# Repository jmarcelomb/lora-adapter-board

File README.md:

Adataper board for [LoRa LLCC68 module](https://pt.aliexpress.com/item/1005005763543912.html?gatewayAdapt=glo2bra) with 2 mm pin spacing.

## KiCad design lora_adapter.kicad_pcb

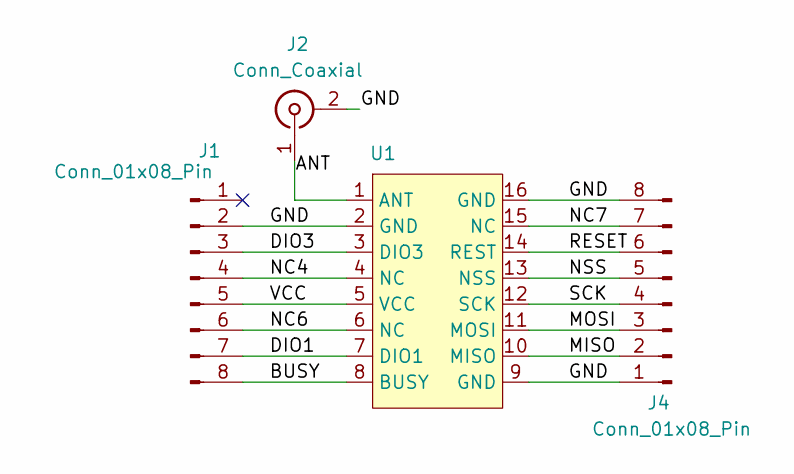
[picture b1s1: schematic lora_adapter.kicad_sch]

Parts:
J1, J4: Conn_01x08_Pin; PinHeader_1x08_P2.54mm_Vertical
J2: Conn_Coaxial; U.FL_Molex_MCRF_73412-0110_Vertical
U1: HOPERF_RFM9XW_SMD

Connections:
/ANT: J2.1 (In), U1.1 (ANT)
/BUSY: J1.8, U1.8 (BUSY)
/DIO1: J1.7, U1.7 (DIO1)
/DIO3: J1.3, U1.3 (DIO3)
/GND: J1.2, J2.2 (Ext), J4.1, J4.8, U1.2 (GND), U1.9 (GND), U1.16 (GND)
/MISO: J4.2, U1.10 (MISO)
/MOSI: J4.3, U1.11 (MOSI)
/NC4: J1.4, U1.4 (NC)
/NC6: J1.6, U1.6 (NC)
/NC7: J4.7, U1.15 (NC)
/NSS: J4.5, U1.13 (NSS)
/RESET: J4.6, U1.14 (REST)
/SCK: J4.4, U1.12 (SCK)
/VCC: J1.5, U1.5 (VCC)

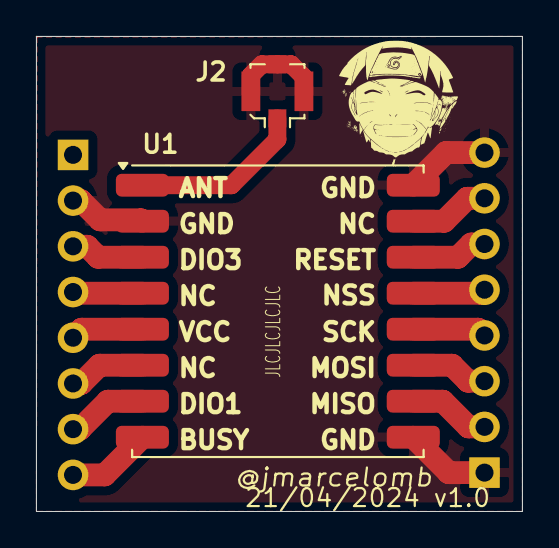
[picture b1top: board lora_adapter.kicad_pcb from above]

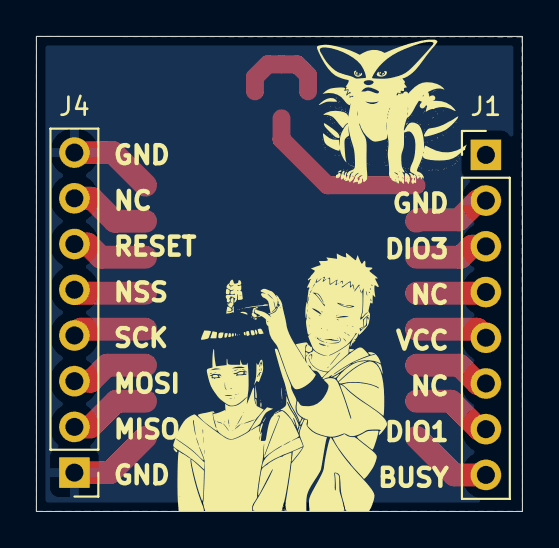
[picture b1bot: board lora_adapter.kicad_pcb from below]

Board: 2 copper layers, 27.0 x 26.4 mm, 4 parts (2 on the bottom side), 14 nets.

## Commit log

2024-06-16 Adds project
2024-06-16 Adds readme
